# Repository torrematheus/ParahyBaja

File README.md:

# ParahyBaja
 Hardware, Firmware e Documentação

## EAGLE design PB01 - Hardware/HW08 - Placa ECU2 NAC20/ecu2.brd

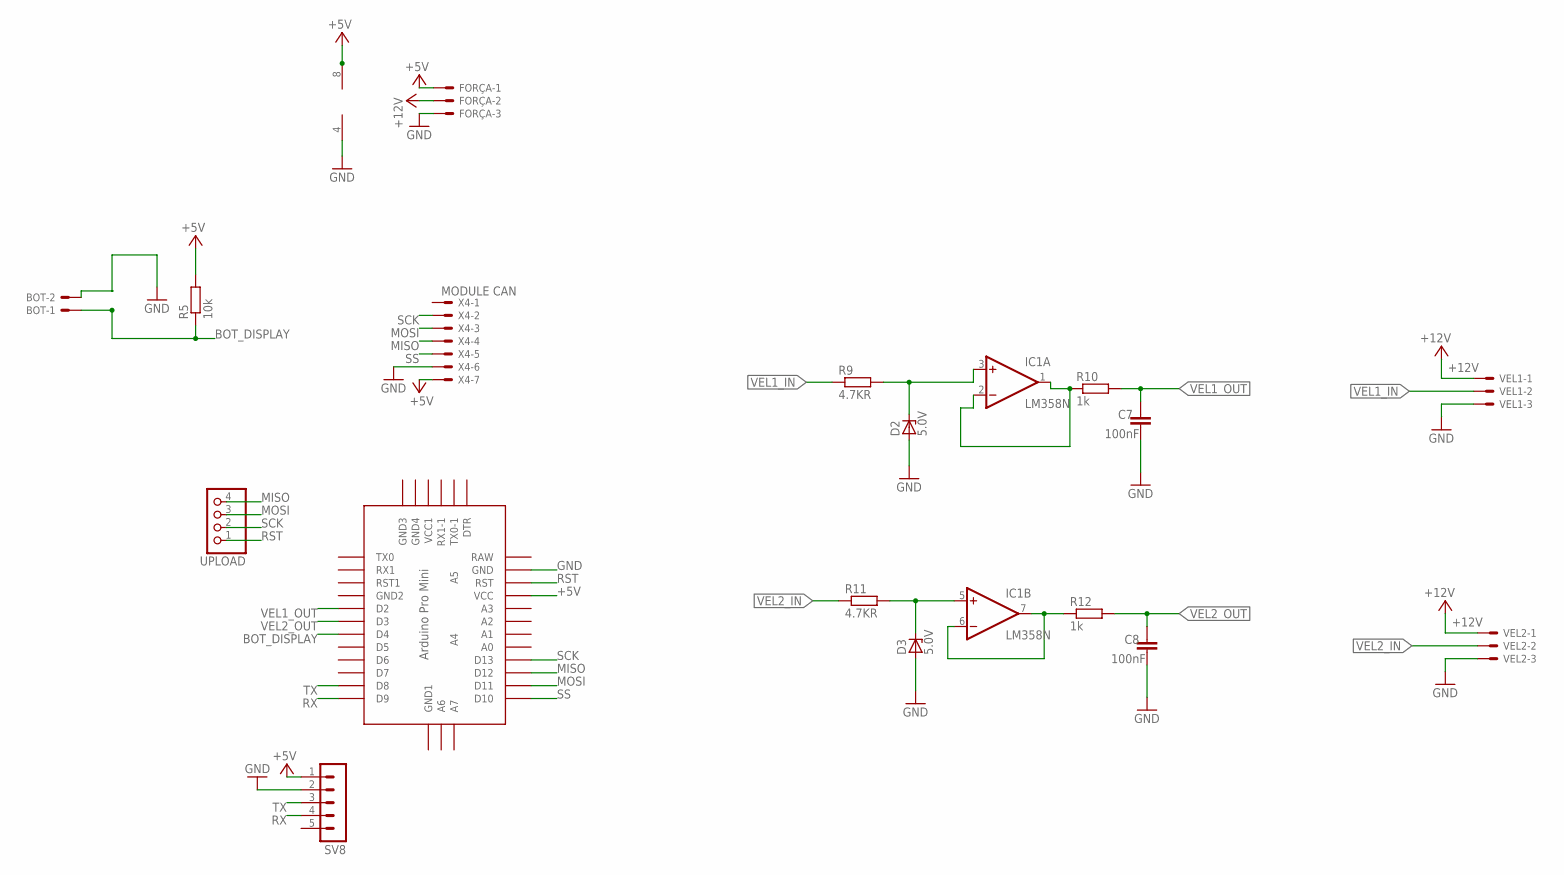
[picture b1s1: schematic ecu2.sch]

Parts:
BOT: RPM; 22-23-2021
C7, C8: 100nF; C5B2.5
D2, D3: 5.0V; DO34Z7
FORÇA: FORÇA; 22-23-2031
IC1: LM358N; DIL08
R5: 10k; 0207/7
R9, R11: 4.7KR; 0207/7
R10, R12: 1k; 0207/7
SV8: MA05-1
U$1: ABK-PRO-MINI
UPLOAD: PINHD-1X4; 1X04
VEL1: COMB 1; 22-23-2031
VEL2: COMB 2; 22-23-2031
X4: MODULE CAN; 22-23-2071

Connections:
+5V: FORÇA.1, IC1.8 (V+), R5.2, SV8.1, U$1.VCC, X4.7; also elsewhere on the board
+12V: FORÇA.2, VEL1.1, VEL2.1
BOT_DISPLAY: BOT.1, R5.1, U$1.D4
GND: BOT.2, C7.1, C8.1, D2.A, D3.A, FORÇA.3, IC1.4 (V-), SV8.2, U$1.GND, VEL1.3, VEL2.3, X4.6; also elsewhere on the board
LEDS: U$1.D6; also elsewhere on the board
MISO: U$1.D12, UPLOAD.4, X4.4
MOSI: U$1.D11, UPLOAD.3, X4.3
unnamed: D2.C, IC1.3 (+IN), R9.2
unnamed: IC1.1 (OUT), IC1.2 (-IN), R10.1
unnamed: D3.C, IC1.5 (+IN), R11.2
unnamed: IC1.6 (-IN), IC1.7 (OUT), R12.1
RST: U$1.RST, UPLOAD.1
RX: SV8.4, U$1.D9
SCK: U$1.D13, UPLOAD.2, X4.2
SS: U$1.D10, X4.5
TX: SV8.3, U$1.D8
VEL1_IN: R9.1, VEL1.2
VEL1_OUT: C7.2, R10.2, U$1.D2
VEL2_IN: R11.1, VEL2.2
VEL2_OUT: C8.2, R12.2, U$1.D3

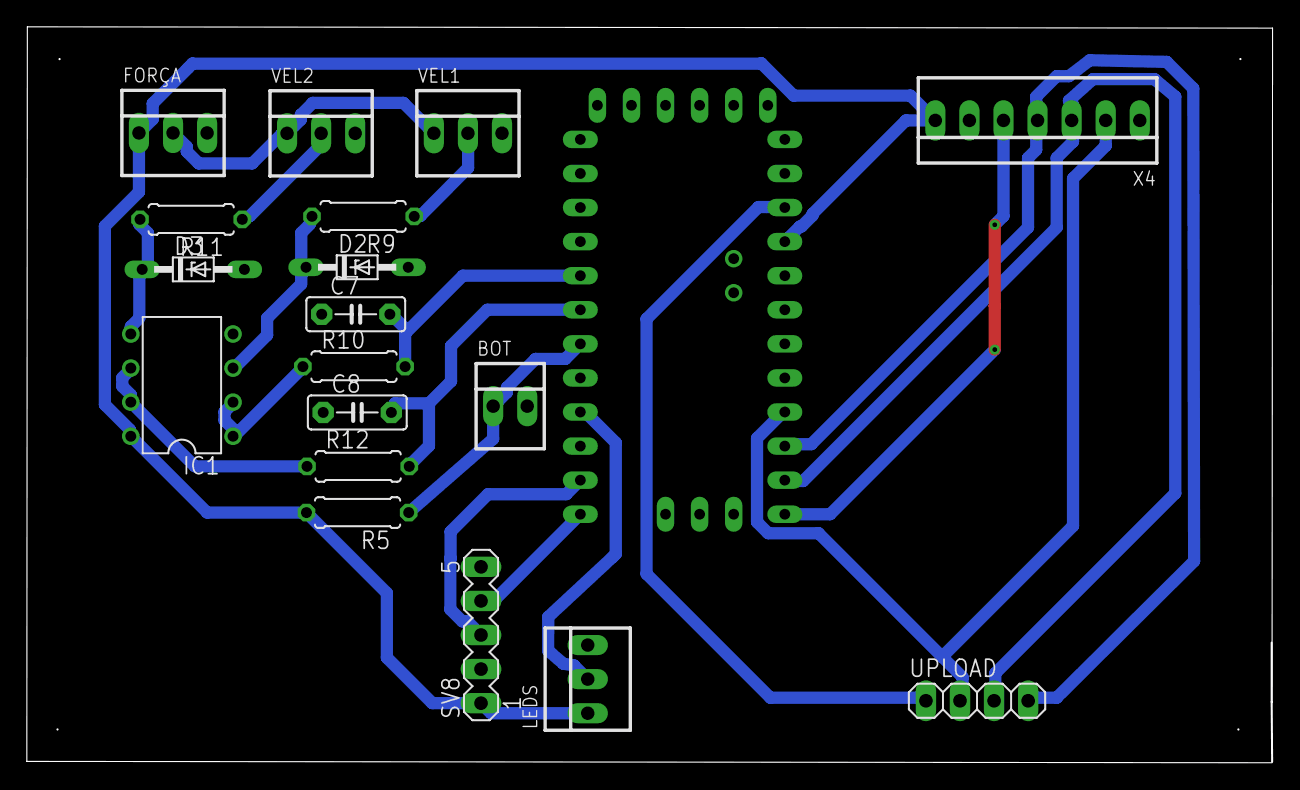
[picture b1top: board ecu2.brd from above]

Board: 2 copper layers, 92.9 x 54.9 mm, 19 parts (0 on the bottom side), 20 nets.

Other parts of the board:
LEDS: FORÇA; 22-23-2031

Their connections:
+5V: LEDS.1; also elsewhere on the board
GND: LEDS.3; also elsewhere on the board
LEDS: LEDS.2; also elsewhere on the board

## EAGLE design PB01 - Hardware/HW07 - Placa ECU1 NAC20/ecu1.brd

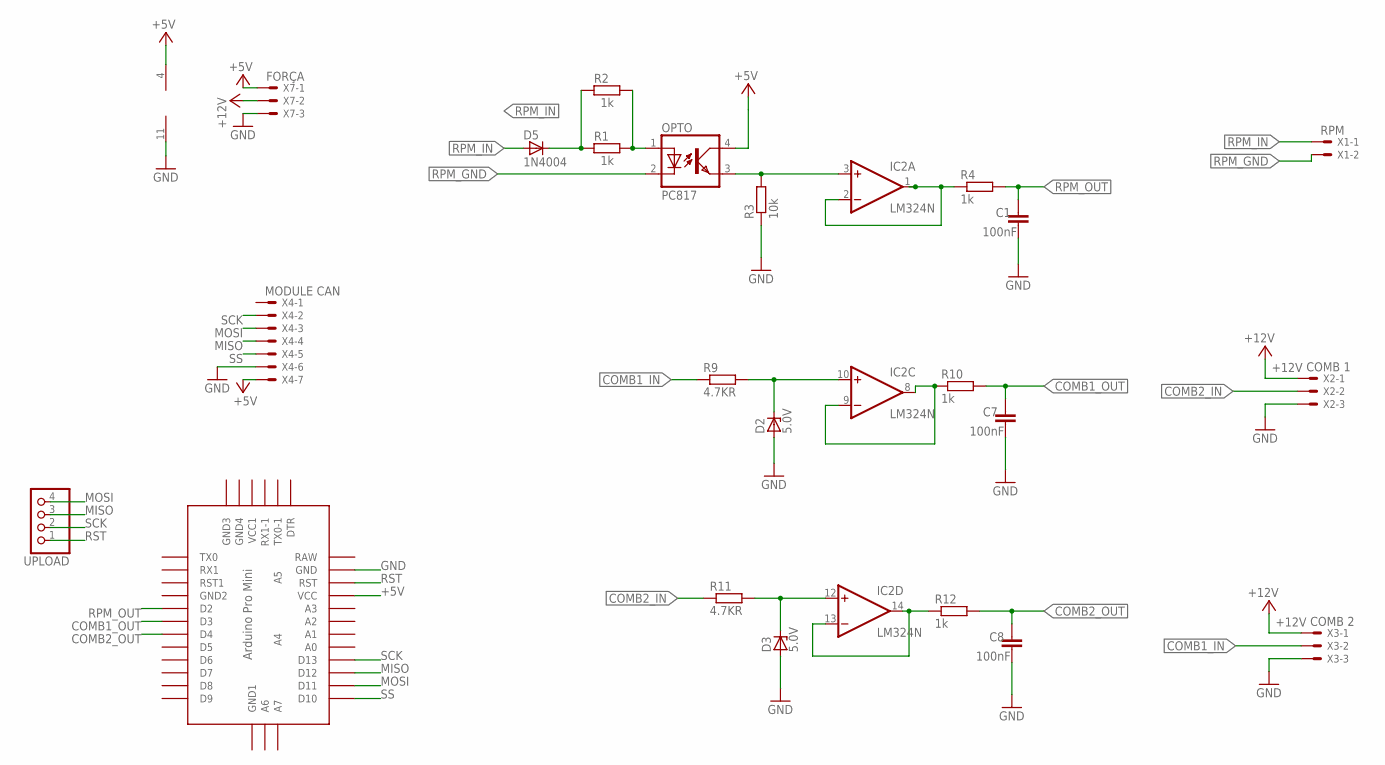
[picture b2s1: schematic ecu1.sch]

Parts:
C1, C7, C8: 100nF; C5B2.5
D2, D3: 5.0V; DO34Z7
D5: 1N4004; DO41-10
IC2: LM324N; DIL14
OPTO: PC817; DIL04
R1, R2, R4, R10, R12: 1k; 0207/7
R3: 10k; 0207/7
R9, R11: 4.7KR; 0207/7
U$1: ABK-PRO-MINI
UPLOAD: PINHD-1X4; 1X04
X1: RPM; 22-23-2021
X2: COMB 1; 22-23-2031
X3: COMB 2; 22-23-2031
X4: MODULE CAN; 22-23-2071
X7: FORÇA; 22-23-2031

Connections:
+5V: IC2.4 (V+), OPTO.4 (COL), U$1.VCC, X4.7, X7.1
+12V: X2.1, X3.1, X7.2
COMB1_IN: R9.1, X3.2
COMB1_OUT: C7.2, R10.2, U$1.D3
COMB2_IN: R11.1, X2.2
COMB2_OUT: C8.2, R12.2, U$1.D4
GND: C1.1, C7.1, C8.1, D2.A, D3.A, IC2.11 (V-), R3.1, U$1.GND, X2.3, X3.3, X4.6, X7.3
MISO: U$1.D12, UPLOAD.3, X4.4
MOSI: U$1.D11, UPLOAD.4, X4.3
unnamed: OPTO.1 (A), R1.2, R2.2
unnamed: D5.C, R1.1, R2.1
unnamed: IC2.1 (OUT), IC2.2 (-IN), R4.1
unnamed: D2.C, IC2.10 (+IN), R9.2
unnamed: IC2.3 (+IN), OPTO.3 (EMIT), R3.2
unnamed: IC2.8 (OUT), IC2.9 (-IN), R10.1
unnamed: D3.C, IC2.12 (+IN), R11.2
unnamed: IC2.13 (-IN), IC2.14 (OUT), R12.1
RPM_GND: OPTO.2 (C), X1.2
RPM_IN: D5.A, X1.1
RPM_OUT: C1.2, R4.2, U$1.D2
RST: U$1.RST, UPLOAD.1
SCK: U$1.D13, UPLOAD.2, X4.2
SS: U$1.D10, X4.5

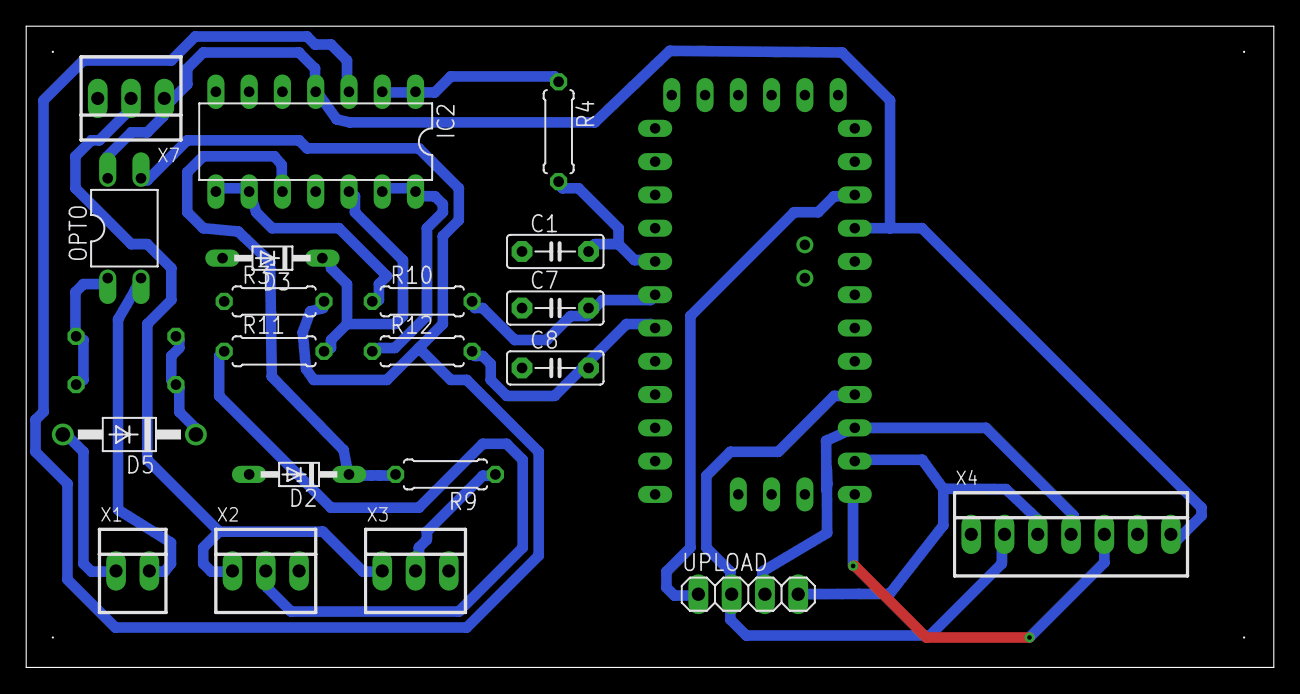
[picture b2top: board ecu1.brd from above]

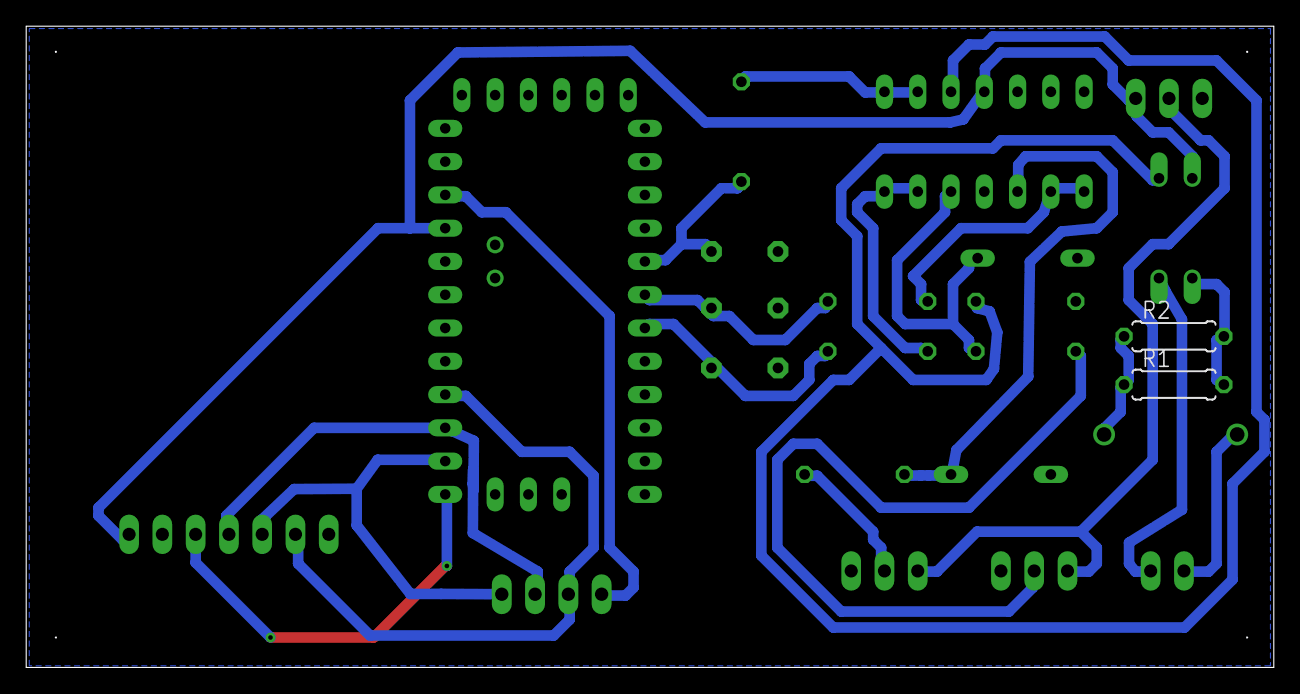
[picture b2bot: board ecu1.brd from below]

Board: 2 copper layers, 95.2 x 48.9 mm, 23 parts (2 on the bottom side), 23 nets.

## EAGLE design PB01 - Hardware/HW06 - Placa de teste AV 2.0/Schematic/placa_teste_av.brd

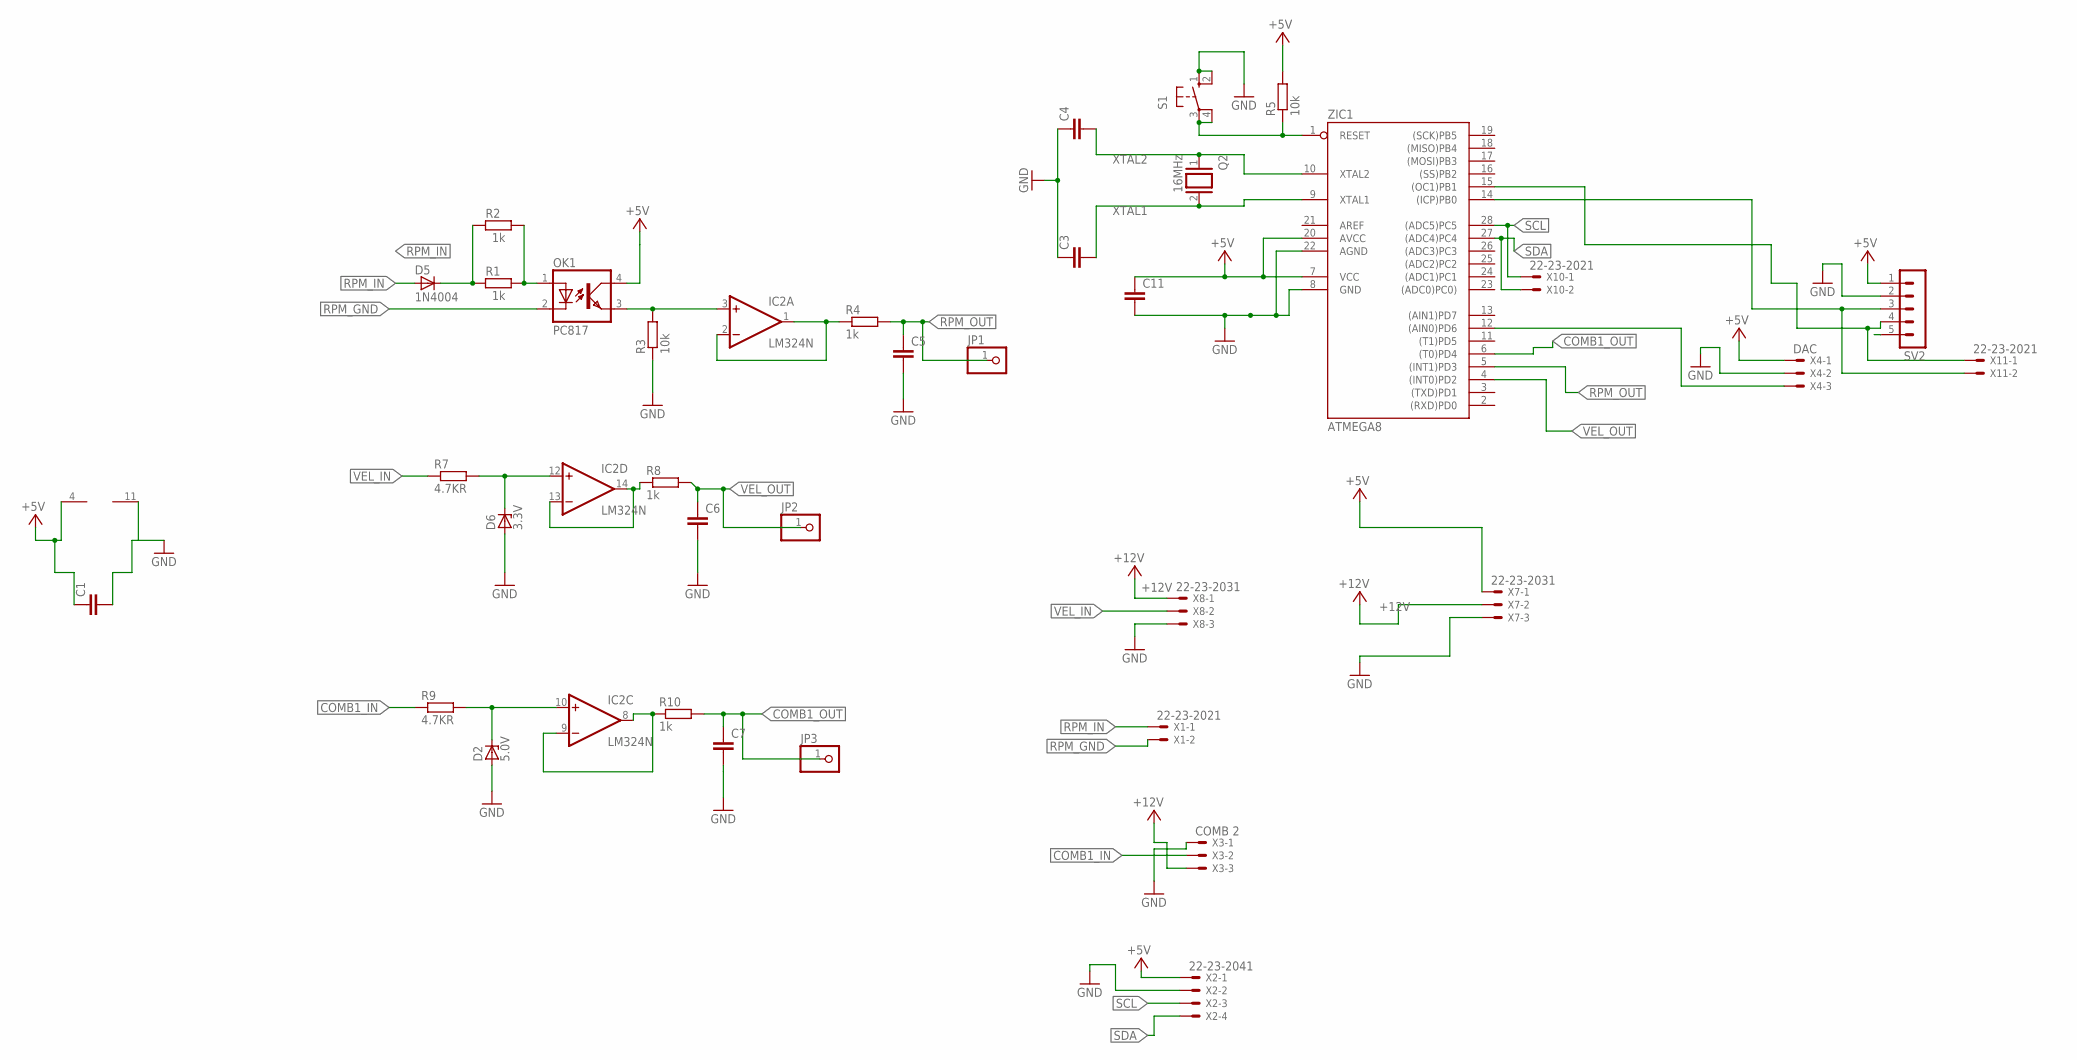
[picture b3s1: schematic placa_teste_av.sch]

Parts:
C1, C5, C6, C7, C11: C5/2.5; C5B2.5
C3, C4: C-EU025-024X044; C025-024X044
D2: 5.0V; DO34Z7
D5: 1N4004; DO41-10
D6: 3.3V; DO34Z7
IC2: LM324N; DIL14
JP1, JP2, JP3: PINHD-1X1; 1X01
OK1: PC817; DIL04
Q2: 16MHz; QS
R1, R2, R4, R8, R10: 1k; 0207/7
R3, R5: 10k; 0207/7
R7, R9: 4.7KR; 0207/7
S1: 10-XX; B3F-10XX
SV2: MA05-1
X1, X10, X11: 22-23-2021
X2: 22-23-2041
X3: COMB 2; 22-23-2031
X4: DAC; 22-23-2031
X7, X8: 22-23-2031
ZIC1: ATMEGA8; DIL28-3

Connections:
+5V: C1.1, C11.1, IC2.4 (V+), OK1.4 (COL), R5.2, SV2.1, X2.1, X4.1, X7.1, ZIC1.7 (VCC), ZIC1.20 (AVCC)
+12V: X3.3, X7.2, X8.1
COMB1_IN: R9.1, X3.2
COMB1_OUT: C7.1, JP3.1, R10.2, ZIC1.6 ((T0)PD4)
GND: C1.2, C3.1, C4.1, C5.2, C6.2, C7.2, C11.2, D2.A, D6.A, IC2.11 (V-), R3.1, S1.1 (S), S1.2 (S1), SV2.2, X2.2, X3.1, X4.2, X7.3, X8.3, ZIC1.8 (GND), ZIC1.22 (AGND)
IO1: SV2.3, X11.2, ZIC1.14 ((ICP)PB0)
IO2: SV2.4, X11.1, ZIC1.15 ((OC1)PB1)
unnamed: OK1.1 (A), R1.2, R2.2
unnamed: D5.C, R1.1, R2.1
unnamed: IC2.1 (OUT), IC2.2 (-IN), R4.1
unnamed: D2.C, IC2.10 (+IN), R9.2
unnamed: IC2.3 (+IN), OK1.3 (EMIT), R3.2
unnamed: D6.C, IC2.12 (+IN), R7.2
unnamed: R5.1, S1.3, S1.4 (P1), ZIC1.1 (RESET)
unnamed: X4.3, ZIC1.12 ((AIN0)PD6)
unnamed: IC2.8 (OUT), IC2.9 (-IN), R10.1
PA10: IC2.13 (-IN), IC2.14 (OUT), R8.1
RPM_GND: OK1.2 (C), X1.2
RPM_IN: D5.A, X1.1
RPM_OUT: C5.1, JP1.1, R4.2, ZIC1.5 ((INT1)PD3)
SCL: X2.3, X10.1, ZIC1.28 ((ADC5)PC5)
SDA: X2.4, X10.2, ZIC1.27 ((ADC4)PC4)
VEL_IN: R7.1, X8.2
VEL_OUT: C6.1, JP2.1, R8.2, ZIC1.4 ((INT0)PD2)
XTAL1: C3.2, Q2.2, ZIC1.9 (XTAL1)
XTAL2: C4.2, Q2.1, ZIC1.10 (XTAL2)

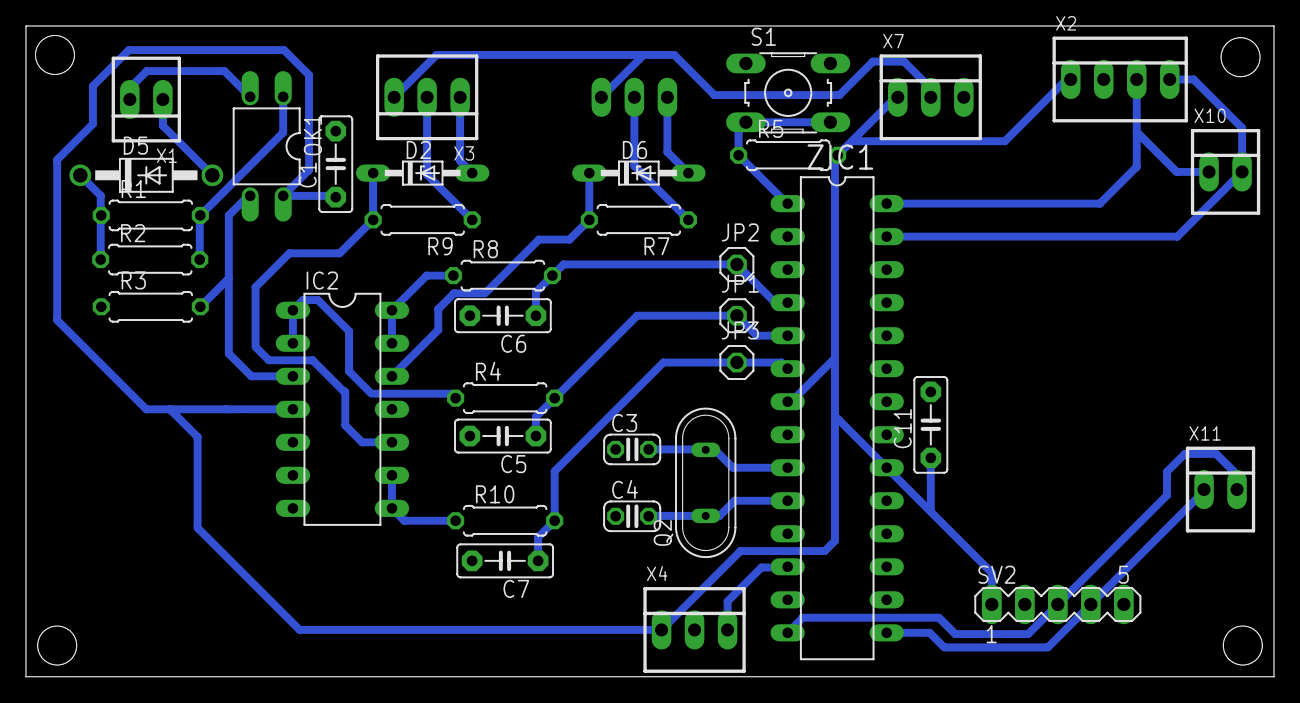
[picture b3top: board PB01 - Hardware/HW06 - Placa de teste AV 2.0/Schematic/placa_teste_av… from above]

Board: 2 copper layers, 96.0 x 50.1 mm, 36 parts (1 on the bottom side), 26 nets.

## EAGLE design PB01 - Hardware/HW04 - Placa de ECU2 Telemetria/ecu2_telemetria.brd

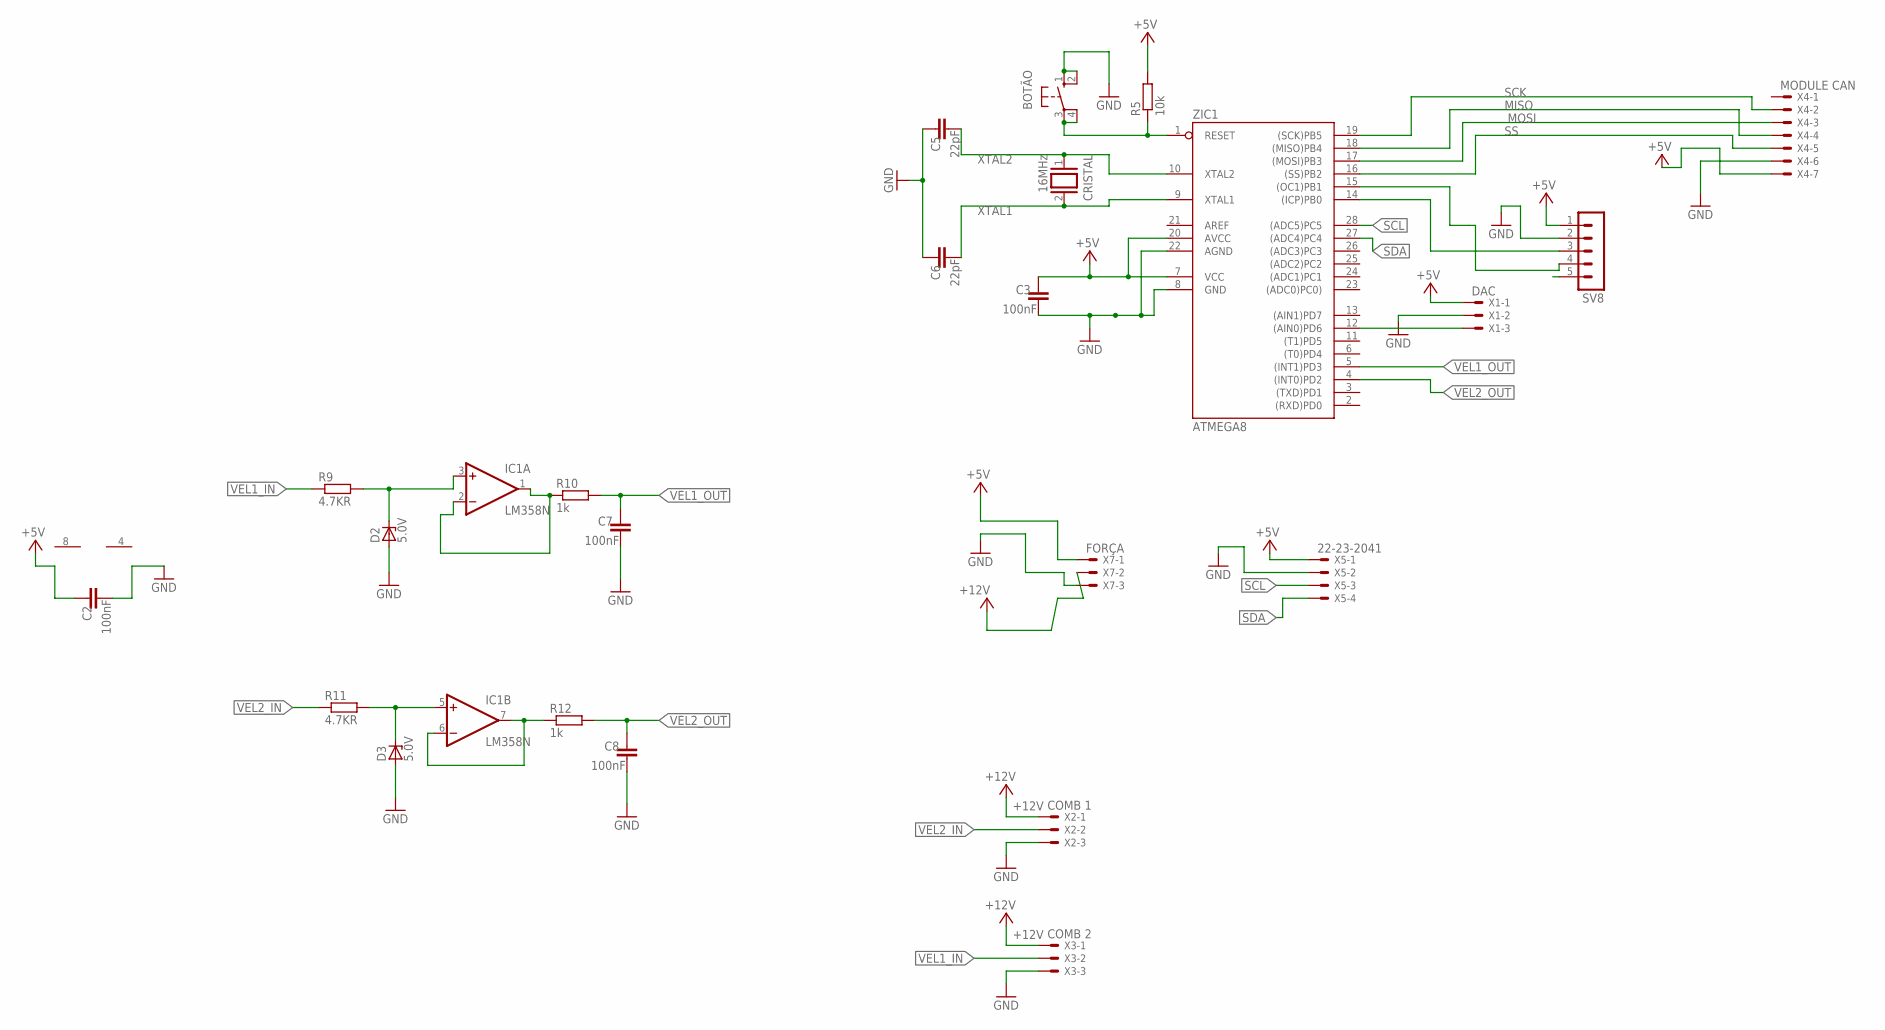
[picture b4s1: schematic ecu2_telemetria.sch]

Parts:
BOTÃO: 10-XX; B3F-10XX
C2, C3, C7, C8: 100nF; C5B2.5
C5, C6: 22pF; C5B2.5
CRISTAL: 16MHz; QS
D2, D3: 5.0V; DO34Z7
IC1: LM358N; DIL08
R5: 10k; 0207/7
R9, R11: 4.7KR; 0207/7
R10, R12: 1k; 0207/7
SV8: MA05-1
X1: DAC; 22-23-2031
X2: COMB 1; 22-23-2031
X3: COMB 2; 22-23-2031
X4: MODULE CAN; 22-23-2071
X5: 22-23-2041
X7: FORÇA; 22-23-2031
ZIC1: ATMEGA8; DIL28-3

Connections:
+5V: C2.2, C3.2, R5.2, SV8.1, X1.1, X4.7, X5.1, X7.1, ZIC1.7 (VCC), ZIC1.20 (AVCC)
+12V: X2.1, X3.1, X7.2
GND: BOTÃO.1 (S), BOTÃO.2 (S1), C2.1, C3.1, C5.2, C6.2, C7.1, C8.1, D2.A, D3.A, SV8.2, X1.2, X2.3, X3.3, X4.6, X5.2, X7.3, ZIC1.8 (GND), ZIC1.22 (AGND)
IO8: SV8.3, ZIC1.14 ((ICP)PB0)
IO9: SV8.4, ZIC1.15 ((OC1)PB1)
MISO: X4.4, ZIC1.18 ((MISO)PB4)
MOSI: X4.3, ZIC1.17 ((MOSI)PB3)
unnamed: X1.3, ZIC1.12 ((AIN0)PD6)
unnamed: D2.C, IC1.3 (+IN), R9.2
unnamed: BOTÃO.3, BOTÃO.4 (P1), R5.1, ZIC1.1 (RESET)
unnamed: IC1.1 (OUT), IC1.2 (-IN), R10.1
unnamed: D3.C, IC1.5 (+IN), R11.2
unnamed: IC1.6 (-IN), IC1.7 (OUT), R12.1
SCK: X4.2, ZIC1.19 ((SCK)PB5)
SCL: X5.3, ZIC1.28 ((ADC5)PC5)
SDA: X5.4, ZIC1.27 ((ADC4)PC4)
SS: X4.5, ZIC1.16 ((SS)PB2)
V+: IC1.8 (V+)
V-: IC1.4 (V-)
VEL1_IN: R9.1, X3.2
VEL1_OUT: C7.2, R10.2, ZIC1.5 ((INT1)PD3)
VEL2_IN: R11.1, X2.2
VEL2_OUT: C8.2, R12.2, ZIC1.4 ((INT0)PD2)
XTAL1: C6.1, CRISTAL.2, ZIC1.9 (XTAL1)
XTAL2: C5.1, CRISTAL.1, ZIC1.10 (XTAL2)

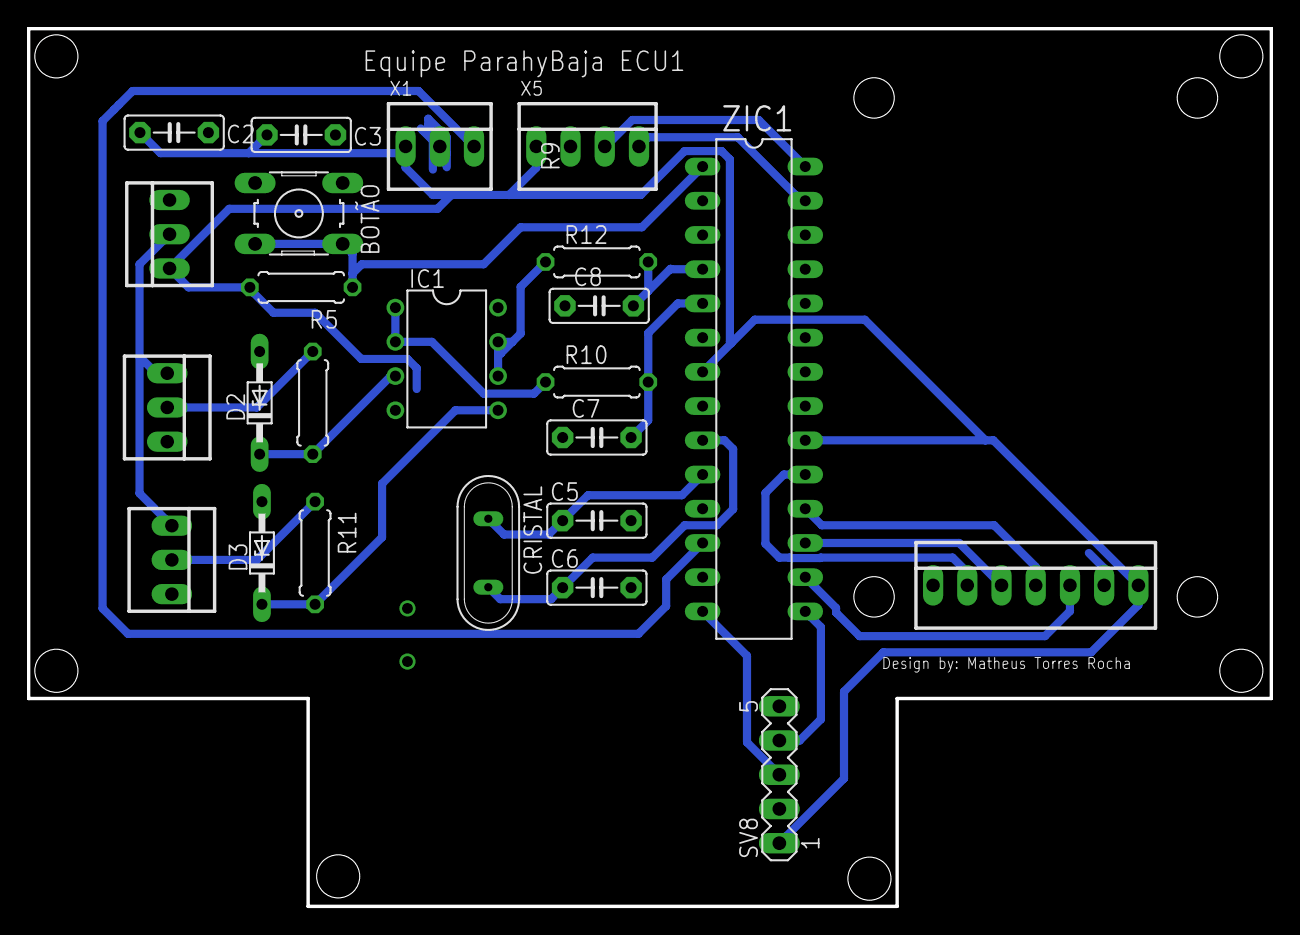
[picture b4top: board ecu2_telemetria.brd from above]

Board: 2 copper layers, 92.2 x 65.2 mm, 24 parts (0 on the bottom side), 23 nets.

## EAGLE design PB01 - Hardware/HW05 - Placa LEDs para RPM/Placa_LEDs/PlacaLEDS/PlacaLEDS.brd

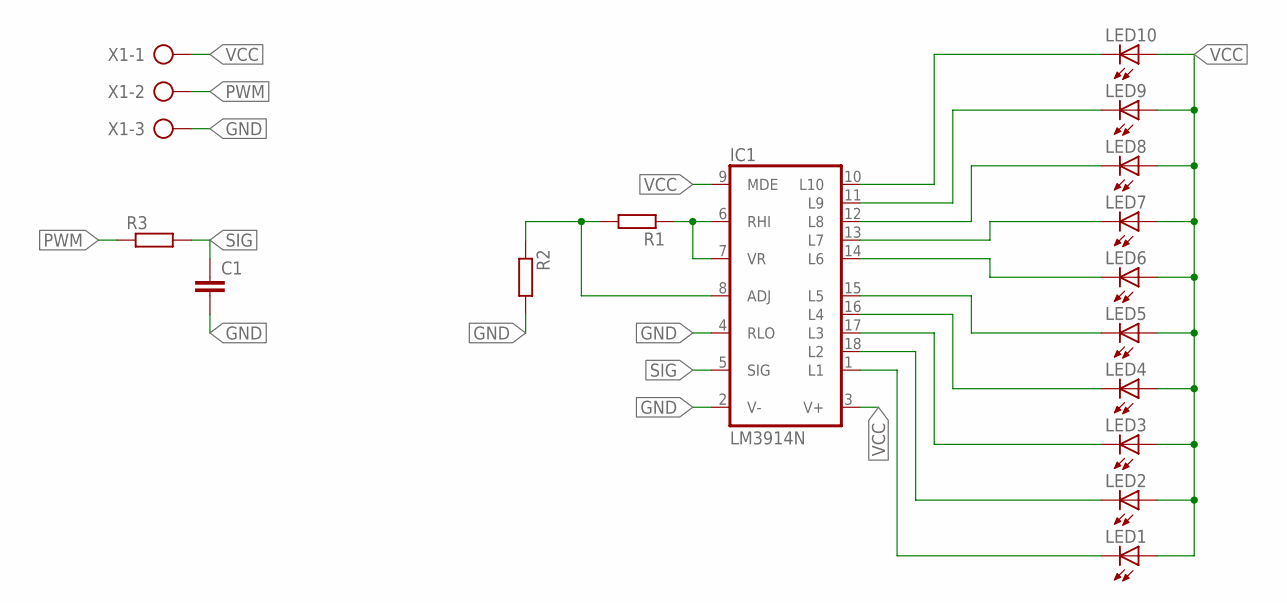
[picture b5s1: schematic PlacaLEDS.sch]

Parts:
C1: C-EU025-050X050; C025-050X050
IC1: LM3914N; DIL18
LED1, LED2, LED3, LED4, LED5, LED6, LED7, LED8, LED9, LED10: LED5MM
R1, R2, R3: R-EU_0204/7; 0204/7
X1: AK500/3

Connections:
GND: C1.2, IC1.2 (V-), IC1.4 (RLO), R2.2, X1.3
unnamed: IC1.10 (L10), LED10.K (C)
unnamed: IC1.11 (L9), LED9.K (C)
unnamed: IC1.12 (L8), LED8.K (C)
unnamed: IC1.13 (L7), LED7.K (C)
unnamed: IC1.14 (L6), LED6.K (C)
unnamed: IC1.15 (L5), LED5.K (C)
unnamed: IC1.16 (L4), LED4.K (C)
unnamed: IC1.17 (L3), LED3.K (C)
unnamed: IC1.18 (L2), LED2.K (C)
unnamed: IC1.1 (L1), LED1.K (C)
unnamed: IC1.6 (RHI), IC1.7 (VR), R1.1
unnamed: IC1.8 (ADJ), R1.2, R2.1
PWM: R3.1, X1.2
SIG: C1.1, IC1.5 (SIG), R3.2
VCC: IC1.3 (V+), IC1.9 (MDE), LED1.A, LED2.A, LED3.A, LED4.A, LED5.A, LED6.A, LED7.A, LED8.A, LED9.A, LED10.A, X1.1

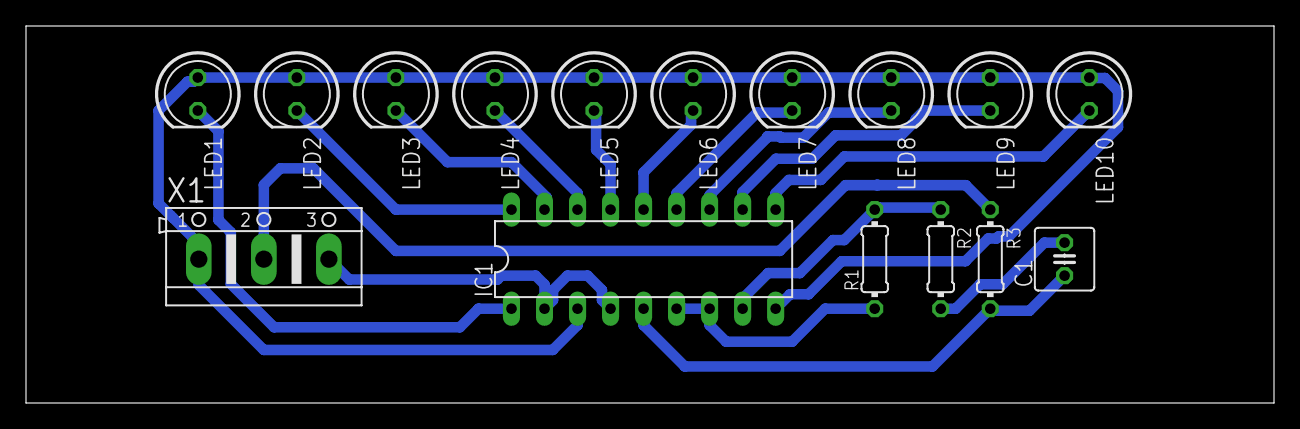
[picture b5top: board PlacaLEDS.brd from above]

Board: 2 copper layers, 96.0 x 29.0 mm, 16 parts (0 on the bottom side), 16 nets.

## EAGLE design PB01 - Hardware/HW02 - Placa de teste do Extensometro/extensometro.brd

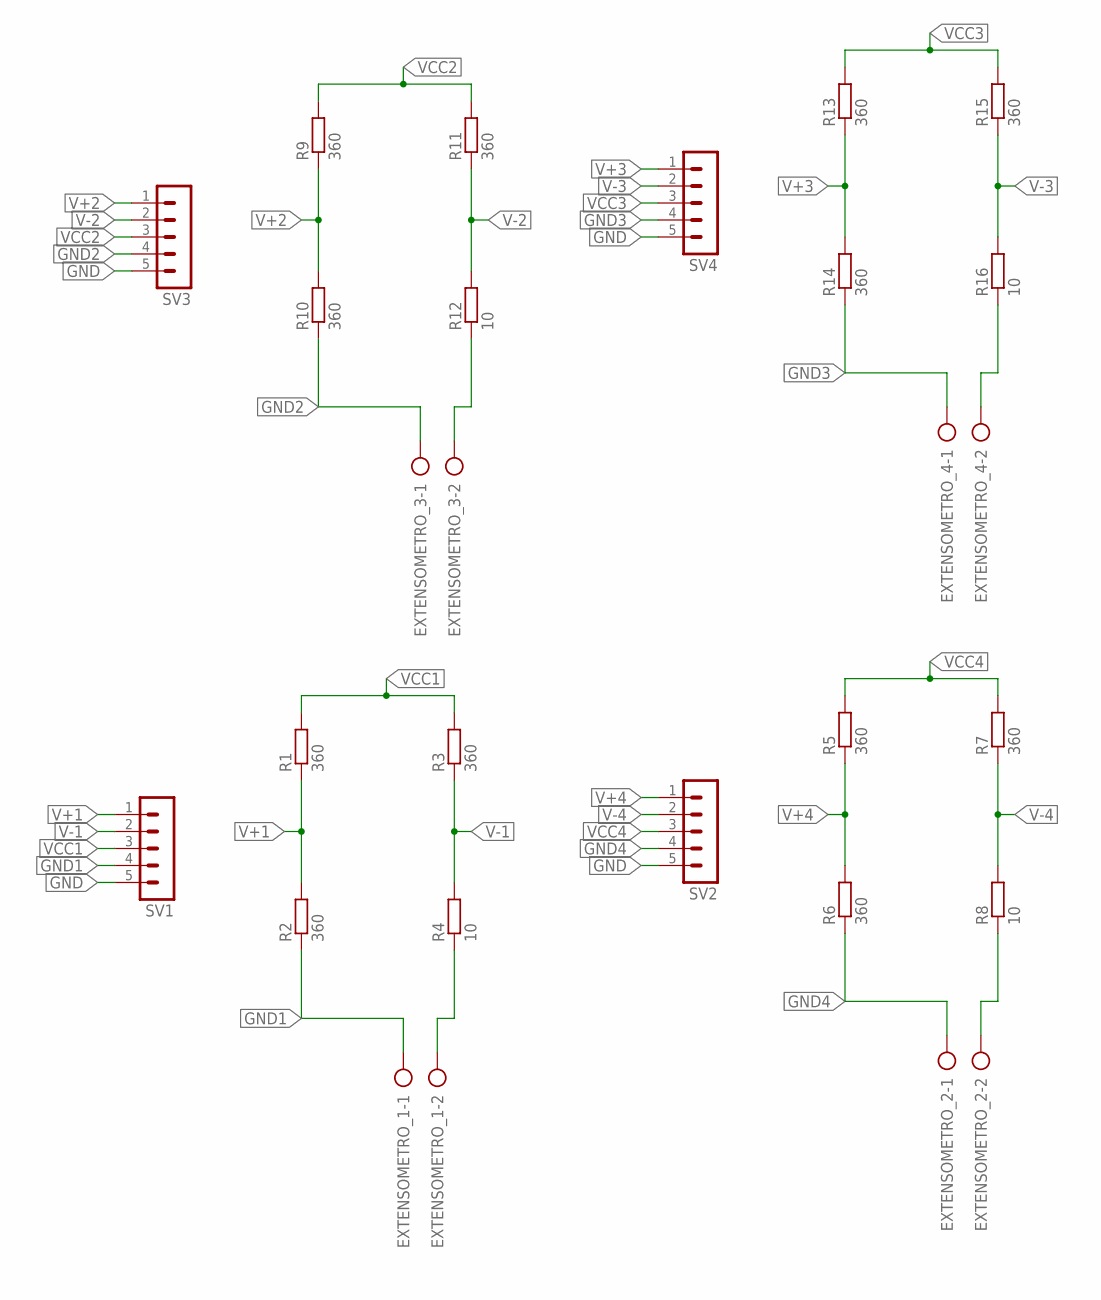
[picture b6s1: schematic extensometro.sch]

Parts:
EXTENSOMETRO_1, EXTENSOMETRO_2, EXTENSOMETRO_3, EXTENSOMETRO_4: AK500/2
R1, R2, R3, R5, R6, R7, R9, R10, R11, R13, R14, R15: 360; 0207/7
R4, R8, R12, R16: 10; 0207/7
SV1, SV2, SV3, SV4: MA05-1

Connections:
GND: SV1.5, SV2.5, SV3.5, SV4.5
GND1: EXTENSOMETRO_1.1, R2.1, SV1.4
GND2: EXTENSOMETRO_3.1, R10.1, SV3.4
GND3: EXTENSOMETRO_4.1, R14.1, SV4.4
GND4: EXTENSOMETRO_2.1, R6.1, SV2.4
unnamed: EXTENSOMETRO_2.2, R8.1
unnamed: EXTENSOMETRO_1.2, R4.1
unnamed: EXTENSOMETRO_3.2, R12.1
unnamed: EXTENSOMETRO_4.2, R16.1
V+1: R1.1, R2.2, SV1.1
V+2: R9.1, R10.2, SV3.1
V+3: R13.1, R14.2, SV4.1
V+4: R5.1, R6.2, SV2.1
V-1: R3.1, R4.2, SV1.2
V-2: R11.1, R12.2, SV3.2
V-3: R15.1, R16.2, SV4.2
V-4: R7.1, R8.2, SV2.2
VCC1: R1.2, R3.2, SV1.3
VCC2: R9.2, R11.2, SV3.3
VCC3: R13.2, R15.2, SV4.3
VCC4: R5.2, R7.2, SV2.3

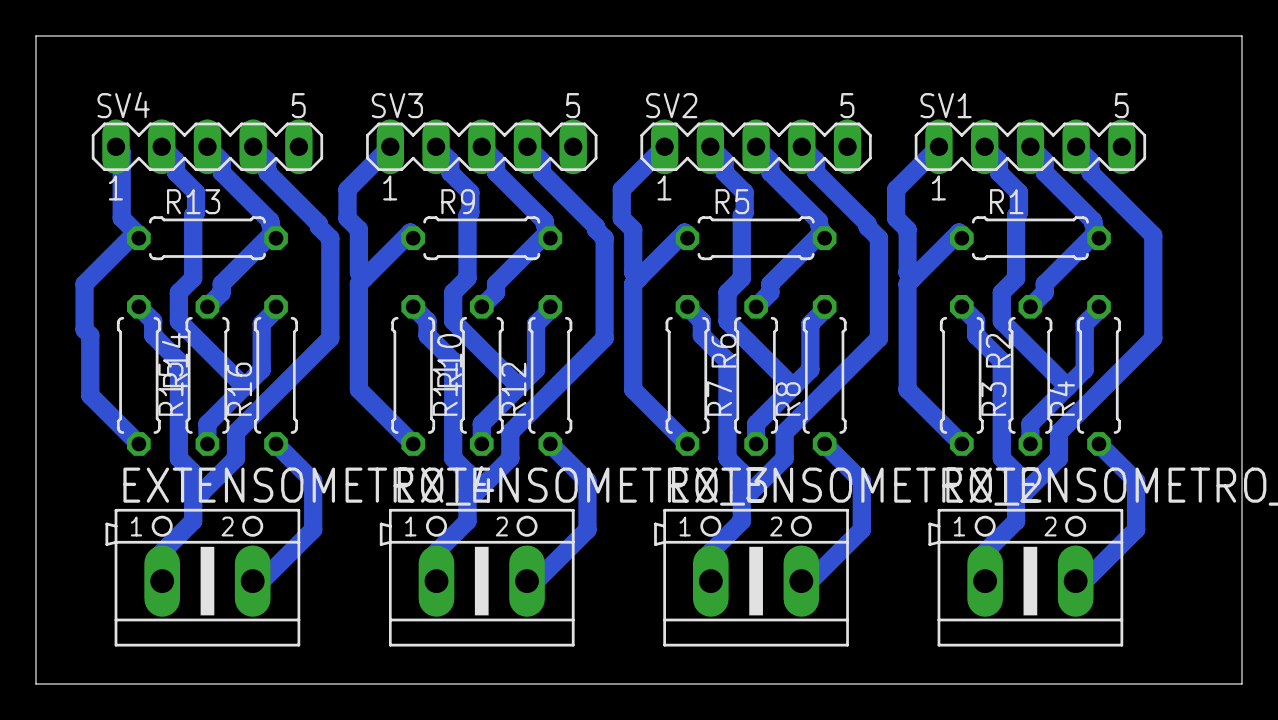
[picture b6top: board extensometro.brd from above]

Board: 2 copper layers, 67.0 x 36.0 mm, 24 parts (0 on the bottom side), 21 nets.

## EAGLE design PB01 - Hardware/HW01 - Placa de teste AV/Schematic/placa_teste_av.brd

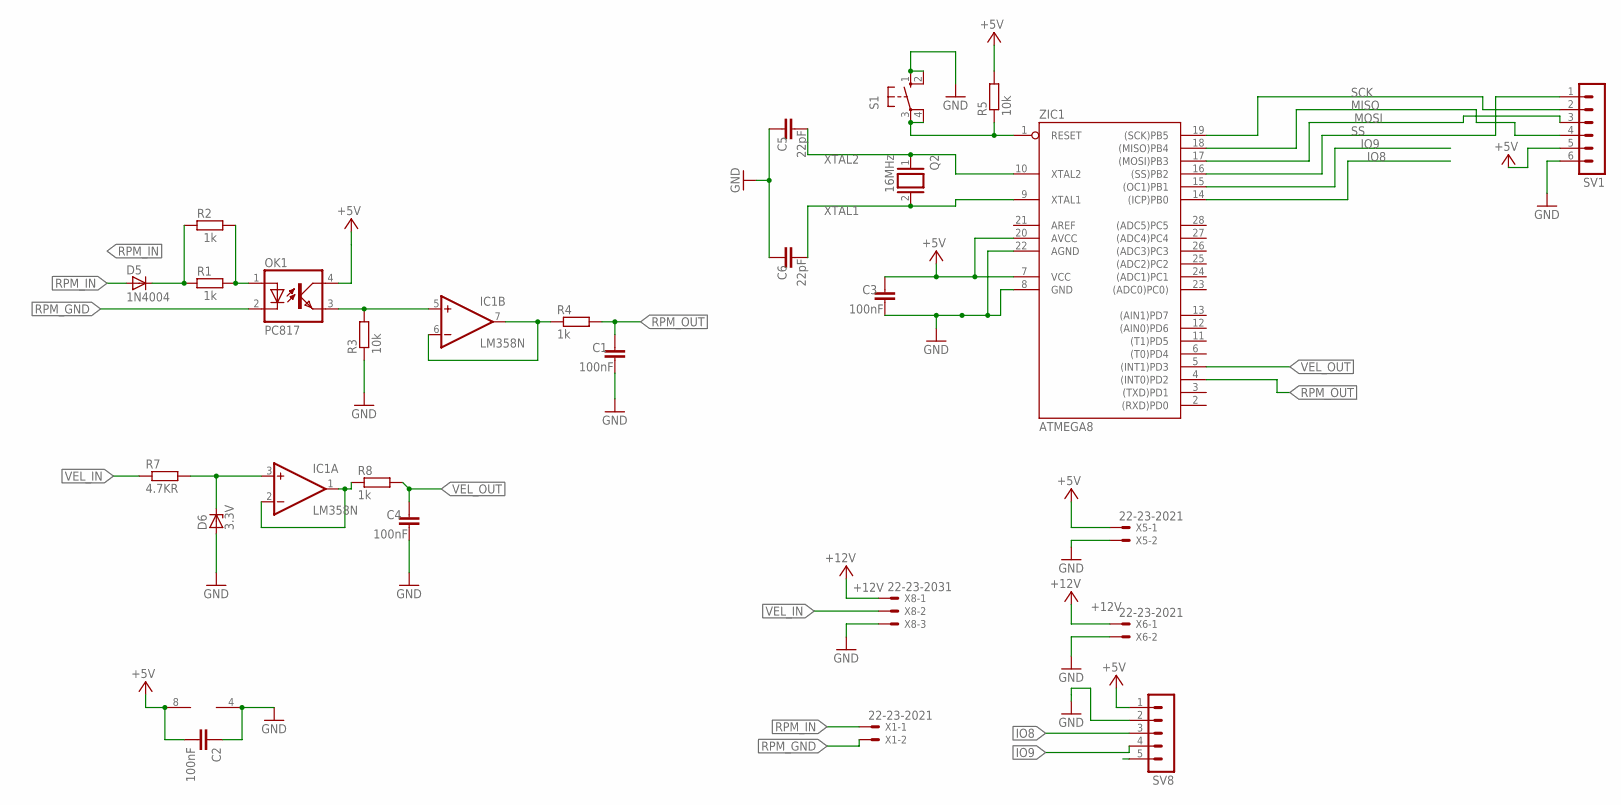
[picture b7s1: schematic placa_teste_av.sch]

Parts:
C1, C3, C4: 100nF; C5B2.5
C2: 100nF; C2.5-3
C5, C6: 22pF; C5B2.5
D5: 1N4004; DO41-10
D6: 3.3V; DO34Z7
IC1: LM358N; DIL08
OK1: PC817; DIL04
Q2: 16MHz; QS
R1, R2, R4, R8: 1k; 0207/7
R3, R5: 10k; 0207/7
R7: 4.7KR; 0207/7
S1: 10-XX; B3F-10XX
SV1: MA06-1
SV8: MA05-1
X1, X5, X6: 22-23-2021
X8: 22-23-2031
ZIC1: ATMEGA8; DIL28-3

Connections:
+5V: C2.2, C3.2, IC1.8 (V+), OK1.4 (COL), R5.2, SV1.5, SV8.1, X5.1, ZIC1.7 (VCC), ZIC1.20 (AVCC)
+12V: X6.1, X8.1
GND: C1.1, C2.1, C3.1, C4.1, C5.2, C6.2, D6.A, IC1.4 (V-), R3.1, S1.1 (S), S1.2 (S1), SV1.6, SV8.2, X5.2, X6.2, X8.3, ZIC1.8 (GND), ZIC1.22 (AGND)
IO8: SV8.3, ZIC1.14 ((ICP)PB0)
IO9: SV8.4, ZIC1.15 ((OC1)PB1)
MISO: SV1.4, ZIC1.18 ((MISO)PB4)
MOSI: SV1.3, ZIC1.17 ((MOSI)PB3)
unnamed: OK1.1 (A), R1.2, R2.2
unnamed: D5.C, R1.1, R2.1
unnamed: IC1.6 (-IN), IC1.7 (OUT), R4.1
unnamed: IC1.5 (+IN), OK1.3 (EMIT), R3.2
unnamed: D6.C, IC1.3 (+IN), R7.2
unnamed: R5.1, S1.3, S1.4 (P1), ZIC1.1 (RESET)
PA10: IC1.1 (OUT), IC1.2 (-IN), R8.1
RPM_GND: OK1.2 (C), X1.2
RPM_IN: D5.A, X1.1
RPM_OUT: C1.2, R4.2, ZIC1.4 ((INT0)PD2)
SCK: SV1.2, ZIC1.19 ((SCK)PB5)
SS: SV1.1, ZIC1.16 ((SS)PB2)
VEL_IN: R7.1, X8.2
VEL_OUT: C4.2, R8.2, ZIC1.5 ((INT1)PD3)
XTAL1: C6.1, Q2.2, ZIC1.9 (XTAL1)
XTAL2: C5.1, Q2.1, ZIC1.10 (XTAL2)
